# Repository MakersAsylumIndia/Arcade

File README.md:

# Arcade
A mini Arcade designed around two custom PCBs - the main board has the Arduino Nano, 128x64 I2C OLED display, and socket headers for digital, analog and PWM GPIO's. 

- The /enclosure folder has 3D FreeCAD model files.
- The /hardware_PCB folders contain schematic, PCB and related files.
- The /code folder has the Arduino code sketches.

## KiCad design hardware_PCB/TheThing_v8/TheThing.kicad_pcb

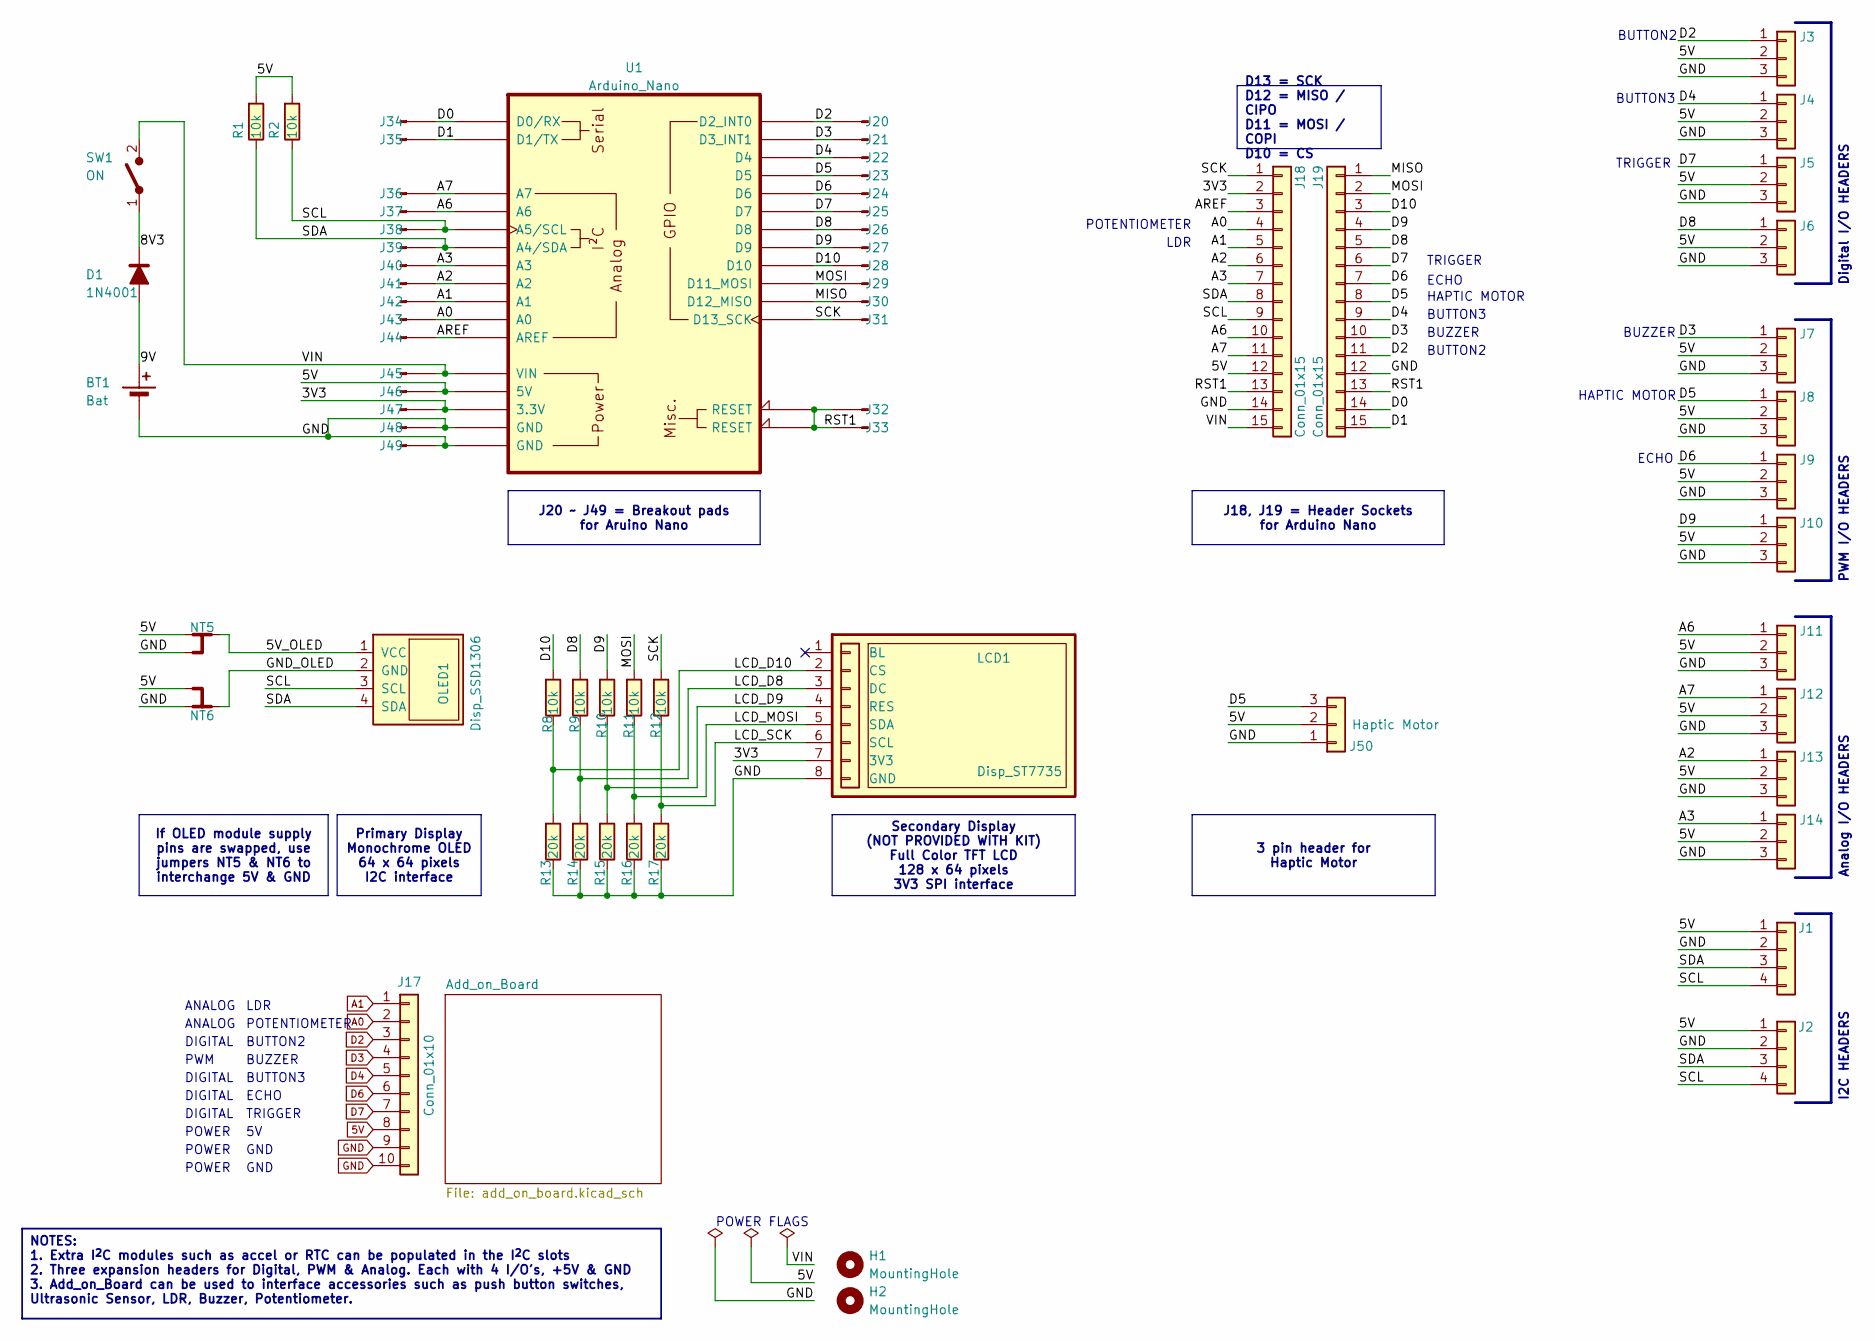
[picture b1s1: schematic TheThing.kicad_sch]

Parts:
BT1: Bat; PinHeader_1x02_P2.54mm_Horizontal
D1: 1N4001; D_DO-41_SOD81_P10.16mm_Horizontal
H1, H2: MountingHole; MountingHole_4.3mm_M4
J1, J2: Conn_I2C; PinHeader_1x04_P2.54mm_Vertical
J3, J4, J5, J6, J7, J8, J9, J10, J11, J12, J13, J14: Conn_01x03; PinHeader_1x03_P2.54mm_Vertical
J17: Conn_01x10; PinHeader_1x10_P2.54mm_Vertical
J18, J19: Conn_01x15; PinSocket_1x15_P2.54mm_Vertical
J20: D2; PinHeader_1x01_P2.54mm_Vertical
J21: D3; PinHeader_1x01_P2.54mm_Vertical
J22: D4; PinHeader_1x01_P2.54mm_Vertical
J23: D5; PinHeader_1x01_P2.54mm_Vertical
J24: D6; PinHeader_1x01_P2.54mm_Vertical
J25: D7; PinHeader_1x01_P2.54mm_Vertical
J26: D8; PinHeader_1x01_P2.54mm_Vertical
J27: D9; PinHeader_1x01_P2.54mm_Vertical
J28: D10; PinHeader_1x01_P2.54mm_Vertical
J29: D11; PinHeader_1x01_P2.54mm_Vertical
J30: D12; PinHeader_1x01_P2.54mm_Vertical
J31: D13; PinHeader_1x01_P2.54mm_Vertical
J32, J33: RST1; PinHeader_1x01_P2.54mm_Vertical
J34: D0; PinHeader_1x01_P2.54mm_Vertical
J35: D1; PinHeader_1x01_P2.54mm_Vertical
J36: A7; PinHeader_1x01_P2.54mm_Vertical
J37: A6; PinHeader_1x01_P2.54mm_Vertical
J38: A5; PinHeader_1x01_P2.54mm_Vertical
J39: A4; PinHeader_1x01_P2.54mm_Vertical
J40: A3; PinHeader_1x01_P2.54mm_Vertical
J41: A2; PinHeader_1x01_P2.54mm_Vertical
J42: A1; PinHeader_1x01_P2.54mm_Vertical
J43: A0; PinHeader_1x01_P2.54mm_Vertical
J44: AREF; PinHeader_1x01_P2.54mm_Vertical
J45: VIN; PinHeader_1x01_P2.54mm_Vertical
J46: 5V; PinHeader_1x01_P2.54mm_Vertical
J47: 3V3; PinHeader_1x01_P2.54mm_Vertical
J48: GND1; PinHeader_1x01_P2.54mm_Vertical
J49: GND2; PinHeader_1x01_P2.54mm_Vertical
J50: Conn_01x03; PinSocket_1x03_P2.54mm_Horizontal_haptic
LCD1: Disp_ST7735; Disp_TFT_LCD_128x128
NT5, NT6: NetTie_3; SolderJumper-3_P1.3mm_Bridged2Bar12_RoundedPad1.0x1.5mm_Num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
OLED1: Disp_SSD1306; Disp_128x64OLED
R1, R2, R8, R9, R10, R11, R12: 10k; R_Axial_DIN0207_L6.3mm_D2.5mm_P7.62mm_Horizontal
R13, R14, R15, R16, R17: 20k; R_Axial_DIN0207_L6.3mm_D2.5mm_P7.62mm_Horizontal
SW1: ON; SW_CuK_OS102011MA1QN1_SPDT_Angled
U1: Arduino_Nano; Arduino_Nano_v2_NoSPI

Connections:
5V: J1.1, J2.1, J3.2, J4.2, J5.2, J6.2, J7.2, J8.2, J9.2, J10.2, J11.2, J12.2, J13.2, J14.2, J17.8, J18.12, J46.1, J50.2, NT5.1, NT6.3, R1.1, R2.1, U1.5V
/3V3: J18.2, J47.1, LCD1.7 (3V3), U1.3V3 (3.3V)
/5V_OLED: NT5.2, OLED1.1 (VCC)
/8V3: D1.1 (K), SW1.1 (A)
/9V: BT1.1 (+), D1.2 (A)
/A2: J13.1, J18.6, J41.1, U1.A2
/A3: J14.1, J18.7, J40.1, U1.A3
/A6: J11.1, J18.10, J37.1, U1.A6
/A7: J12.1, J18.11, J36.1, U1.A7
/AREF: J18.3, J44.1, U1.AREF
/D0: J19.14, J34.1, U1.D0 (D0/RX)
/D1: J19.15, J35.1, U1.D1 (D1/TX)
/D5: J8.1, J19.8, J23.1, J50.3, U1.D5
/D8: J6.1, J19.5, J26.1, R9.1, U1.D8
/D9: J10.1, J19.4, J27.1, R10.1, U1.D9
/D10: J19.3, J28.1, R8.1, U1.D10
/GND_OLED: NT6.2, OLED1.2 (GND)
/LCD_D8: LCD1.3 (DC), R9.2, R14.1
/LCD_D9: LCD1.4 (RES), R10.2, R15.1
/LCD_D10: LCD1.2 (CS), R8.2, R13.1
/LCD_MOSI: LCD1.5 (SDA), R11.2, R16.1
/LCD_SCK: LCD1.6 (SCL), R12.2, R17.1
/MISO: J19.1, J30.1, U1.D12 (D12_MISO)
/MOSI: J19.2, J29.1, R11.1, U1.D11 (D11_MOSI)
/RST1: J18.13, J19.13, J32.1, J33.1, U1.RST1 (RESET), U1.RST2 (RESET)
/SCK: J18.1, J31.1, R12.1, U1.D13 (D13_SCK)
/SCL: J1.4, J2.4, J18.9, J38.1, OLED1.3 (SCL), R2.2, U1.A5 (A5/SCL)
/SDA: J1.3, J2.3, J18.8, J39.1, OLED1.4 (SDA), R1.2, U1.A4 (A4/SDA)
/VIN: J18.15, J45.1, SW1.2 (B), U1.VIN
A0: J17.2, J18.4, J43.1, U1.A0
A1: J17.1, J18.5, J42.1, U1.A1
D2: J3.1, J17.3, J19.11, J20.1, U1.D2 (D2_INT0)
D3: J7.1, J17.4, J19.10, J21.1, U1.D3 (D3_INT1)
D4: J4.1, J17.5, J19.9, J22.1, U1.D4
D6: J9.1, J17.6, J19.7, J24.1, U1.D6
D7: J5.1, J17.7, J19.6, J25.1, U1.D7
GND: BT1.2 (-), J1.2, J2.2, J3.3, J4.3, J5.3, J6.3, J7.3, J8.3, J9.3, J10.3, J11.3, J12.3, J13.3, J14.3, J17.9, J17.10, J18.14, J19.12, J48.1, J49.1, J50.1, LCD1.8 (GND), NT5.3, NT6.1, R13.2, R14.2, R15.2, R16.2, R17.2, U1.GND1 (GND), U1.GND2 (GND)

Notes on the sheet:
DIGITAL
BUTTON3
POWER
TRIGGER
BUZZER
Digital I/O HEADERS
I2C HEADERS
POTENTIOMETER
LDR
POWER FLAGS
PWM
ECHO
PWM I/O HEADERS
ANALOG
Analog I/O HEADERS
GND
HAPTIC MOTOR
BUTTON2
Primary Display Monochrome OLED 64 x 64 pixels I2C interface
D13 = SCK D12 = MISO / CIPO D11 = MOSI / COPI D10 = CS
J18, J19 = Header Sockets for Arduino Nano
3 pin header for Haptic Motor
Secondary Display (NOT PROVIDED WITH KIT) Full Color TFT LCD 128 x 64 pixels 3V3 SPI interface
NOTES: 1. Extra I^{2}C modules such as accel or RTC can be populated in the I^{2}C slots 2. Three expansion headers for Digital, PWM & Analog. Each with 4 I/O's, +5V & GND 3. Add_on_Board can be used to interface accessories such as push button switches, Ultrasonic Sensor, LDR, Buzzer, Potentiomete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
J20 ~ J49 = Breakout pads for Aruino Nano
If OLED module supply pins are swapped, use jumpers NT5 & NT6 to interchange 5V & GND

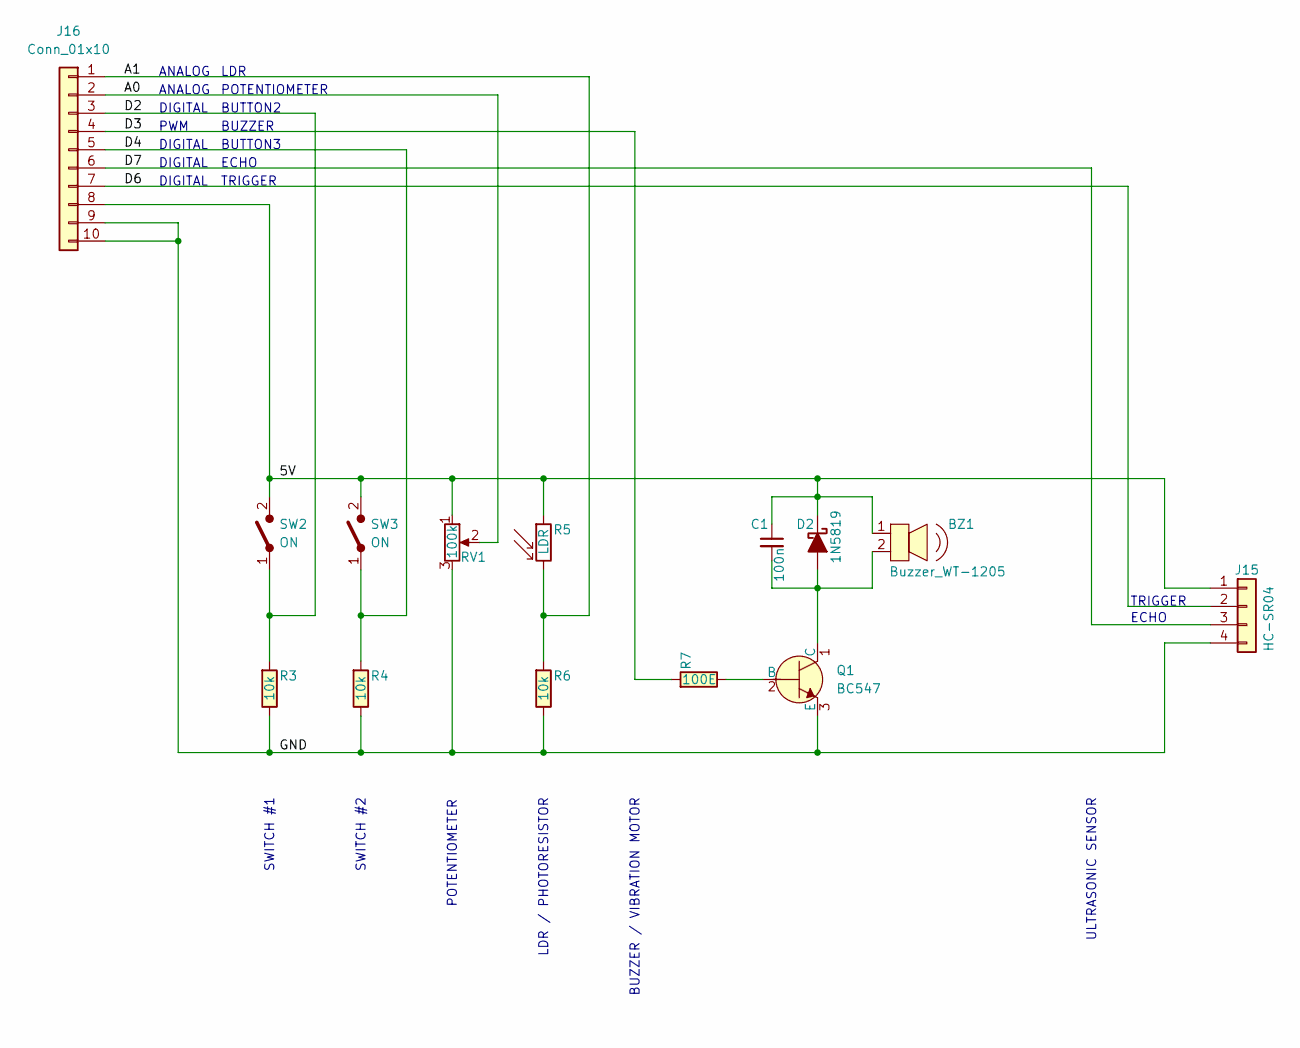
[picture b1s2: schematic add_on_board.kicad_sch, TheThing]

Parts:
BZ1: Buzzer_WT-1205; Buzzer_12x9.5RM7.6; MPN PS1240P02BT
C1: 100n; C_Disc_D3.0mm_W2.0mm_P2.50mm
D2: 1N5819; D_DO-41_SOD81_P10.16mm_Horizontal
J15: HC-SR04; PinSocket_1x04_P2.54mm_Vertical
J16: Conn_01x10; PinHeader_1x10_P2.54mm_Vertical
Q1: BC547; TO-92_HandSolder; MPN BC547B
R3, R4, R6: 10k; R_Axial_DIN0207_L6.3mm_D2.5mm_P7.62mm_Horizontal
R5: LDR; R_LDR_4.9x4.2mm_P2.54mm_Vertical
R7: 100E; R_Axial_DIN0207_L6.3mm_D2.5mm_P7.62mm_Horizontal
RV1: 100k; TRIM_601040
SW2, SW3: ON; SWITCH_PUSH_6mm_12mm

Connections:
/Add_on_Board/5V: BZ1.1, C1.1, D2.1 (K), J15.1, J16.8, R5.1, RV1.1, SW2.2 (B), SW3.2 (B)
/Add_on_Board/A0: J16.2, RV1.2
/Add_on_Board/A1: J16.1, R5.2, R6.1
/Add_on_Board/D2: J16.3, R3.1, SW2.1 (A)
/Add_on_Board/D3: J16.4, R7.1
/Add_on_Board/D4: J16.5, R4.1, SW3.1 (A)
/Add_on_Board/D6: J15.2, J16.7
/Add_on_Board/D7: J15.3, J16.6
/Add_on_Board/GND: J15.4, J16.9, J16.10, Q1.3 (E), R3.2, R4.2, R6.2, RV1.3
unnamed: BZ1.2, C1.2, D2.2 (A), Q1.1 (C)
unnamed: Q1.2 (B), R7.2

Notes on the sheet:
SWITCH #1
BUZZER / VIBRATION MOTOR
SWITCH #2
ULTRASONIC SENSOR
ANALOG
DIGITAL
PWM
BUZZER
BUTTON2
LDR / PHOTORESISTOR
POTENTIOMETER
ECHO
LDR
BUTTON3
TRIGGER

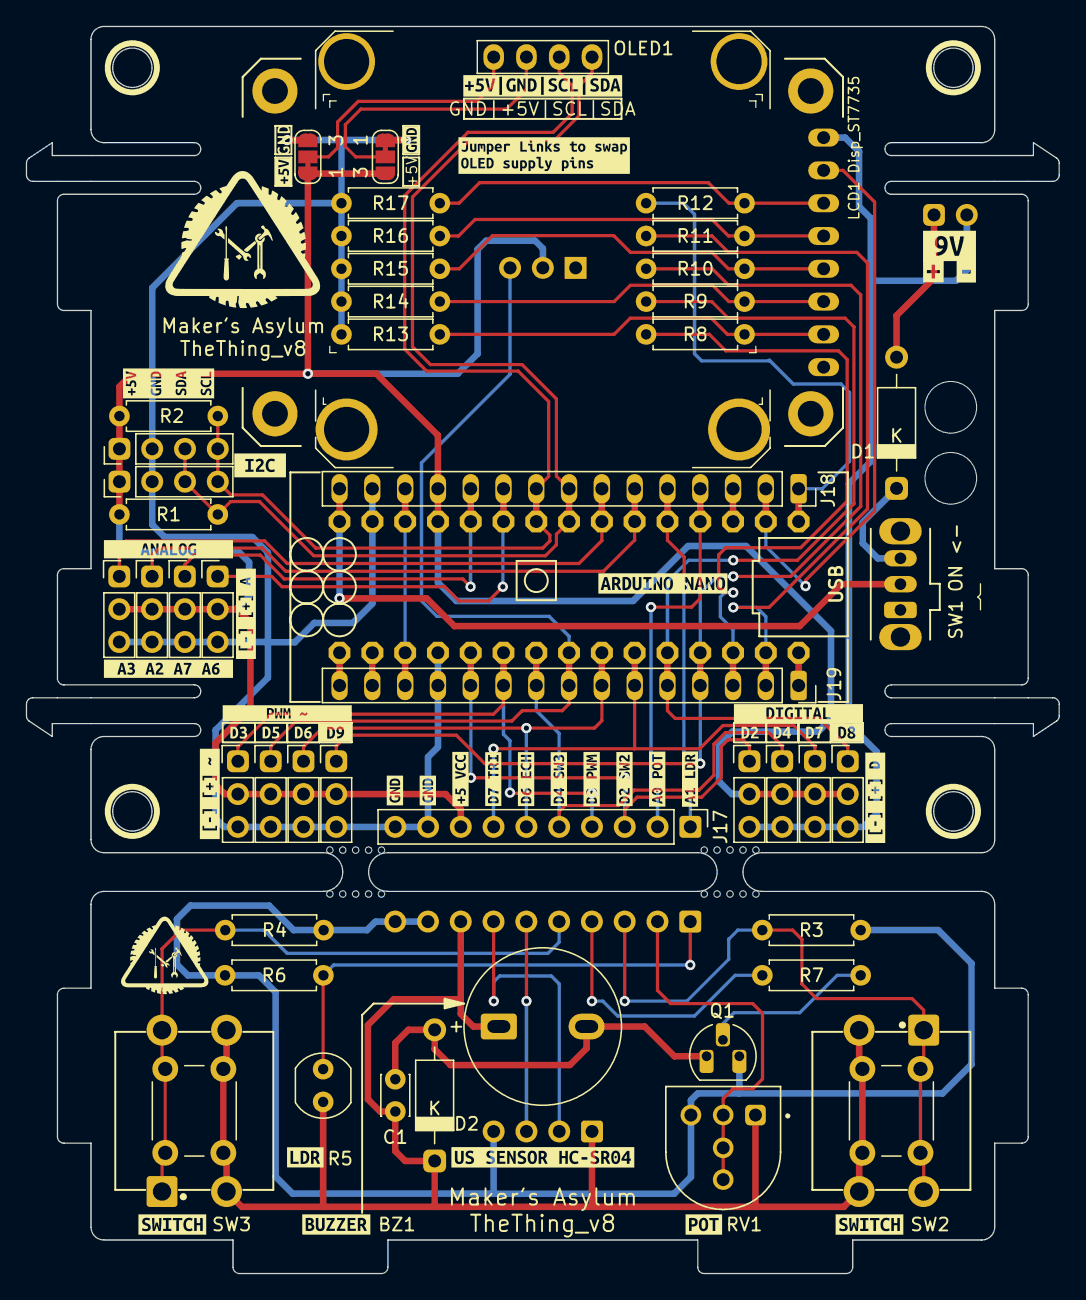
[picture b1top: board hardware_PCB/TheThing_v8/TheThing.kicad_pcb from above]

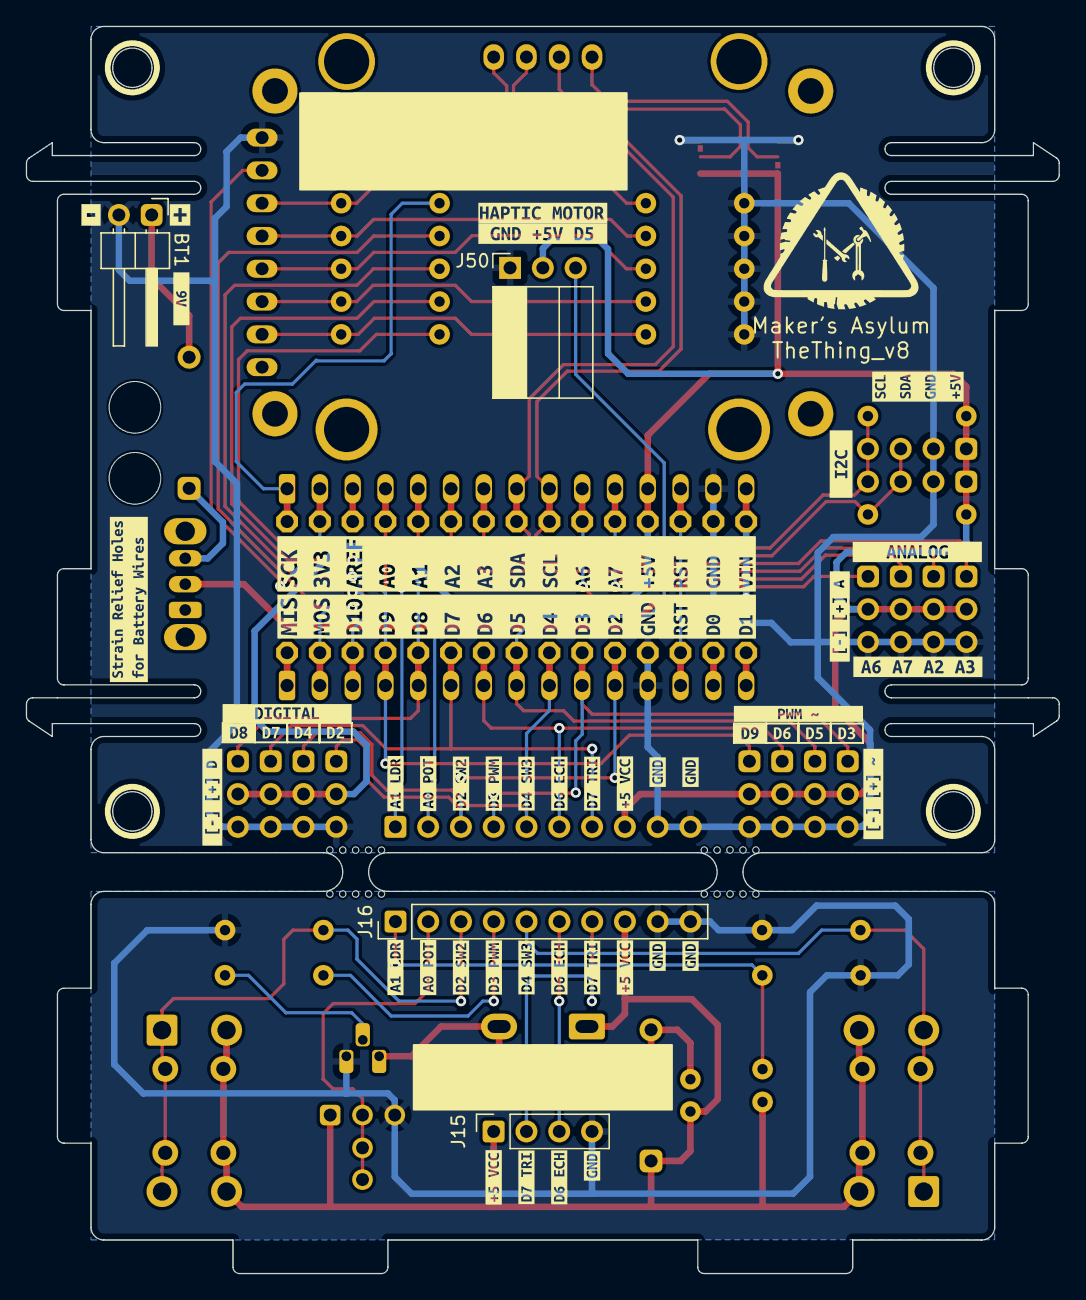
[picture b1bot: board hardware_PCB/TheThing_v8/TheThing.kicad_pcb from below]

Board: 2 copper layers, 80.0 x 96.6 mm, 173 parts (53 on the bottom side), 48 nets.

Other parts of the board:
kibuzzard-67A22DCA: G***; kibuzzard-67A22DCA
kibuzzard-67A22DD3: G***; kibuzzard-67A22DD3
kibuzzard-67A22DDD: G***; kibuzzard-67A22DDD
kibuzzard-67A22DE4: G***; kibuzzard-67A22DE4
kibuzzard-67A22DF7: G***; kibuzzard-67A22DF7
kibuzzard-67A122A3: G***; kibuzzard-67A122A3
kibuzzard-67A122C1: G***; kibuzzard-67A122C1
kibuzzard-67A11942: G***; kibuzzard-67A11942
kibuzzard-67A20273: G***; kibuzzard-67A20273
kibuzzard-681BBDCE: G***; kibuzzard-681BBDCE
kibuzzard-681CE6A6, kibuzzard-681CE6A6#2, kibuzzard-681CE6A6#3: G***; kibuzzard-681CE6A6
kibuzzard-681CE6D9, kibuzzard-681CE6D9#2, kibuzzard-681CE6D9#3: G***; kibuzzard-681CE6D9
kibuzzard-681CE6E0, kibuzzard-681CE6E0#2, kibuzzard-681CE6E0#3: G***; kibuzzard-681CE6E0
kibuzzard-681CE6FF, kibuzzard-681CE6FF#2, kibuzzard-681CE6FF#3: G***; kibuzzard-681CE6FF
kibuzzard-681CE70B, kibuzzard-681CE70B#2, kibuzzard-681CE70B#3: G***; kibuzzard-681CE70B
kibuzzard-681CE705, kibuzzard-681CE705#2, kibuzzard-681CE705#3: G***; kibuzzard-681CE705
kibuzzard-681CE710, kibuzzard-681CE710#2, kibuzzard-681CE710#3: G***; kibuzzard-681CE710
kibuzzard-681CE715, kibuzzard-681CE715#2, kibuzzard-681CE715#3: G***; kibuzzard-681CE715
kibuzzard-681CED7D: G***; kibuzzard-681CED7D
kibuzzard-681CEDBE: G***; kibuzzard-681CEDBE
kibuzzard-681CEE16: G***; kibuzzard-681CEE16
kibuzzard-681CEF1C: G***; kibuzzard-681CEF1C
kibuzzard-681CF111: G***; kibuzzard-681CF111
kibuzzard-681D00EA: G***; kibuzzard-681D00EA
kibuzzard-681D13E1, kibuzzard-681D13E1#2: G***; kibuzzard-681D13E1
kibuzzard-681D14E6, kibuzzard-681D14E6#2: G***; kibuzzard-681D14E6
kibuzzard-681D0124: G***; kibuzzard-681D0124
kibuzzard-681D1422: G***; kibuzzard-681D1422
kibuzzard-687E01B3: G***; kibuzzard-687E01B3
kibuzzard-687E01EA: G***; kibuzzard-687E01EA
kibuzzard-687E01F5: G***; kibuzzard-687E01F5
kibuzzard-687E12B6: G***; kibuzzard-687E12B6
kibuzzard-687E019A: G***; kibuzzard-687E019A
kibuzzard-687E020C: G***; kibuzzard-687E020C
kibuzzard-687E0202: G***; kibuzzard-687E0202
kibuzzard-687E1831: G***; kibuzzard-687E1831
kibuzzard-688B0B7B, kibuzzard-688B0B7B#2: G***; kibuzzard-688B0B7B
kibuzzard-688B0B80, kibuzzard-688B0B80#2: G***; kibuzzard-688B0B80
kibuzzard-688B0B86, kibuzzard-688B0B86#2: G***; kibuzzard-688B0B86
kibuzzard-688B0CB0, kibuzzard-688B0CB0#2: G***; kibuzzard-688B0CB0
kibuzzard-688B1C9E: G***; kibuzzard-688B1C9E
kibuzzard-688B4A2D: G***; kibuzzard-688B4A2D
kibuzzard-688B04F2: G***; kibuzzard-688B04F2
kibuzzard-688B05AD: G***; kibuzzard-688B05AD
kibuzzard-688B06AA, kibuzzard-688B06AA#2: G***; kibuzzard-688B06AA
kibuzzard-688B07C0, kibuzzard-688B07C0#2: G***; kibuzzard-688B07C0
kibuzzard-688B07DB, kibuzzard-688B07DB#2: G***; kibuzzard-688B07DB
kibuzzard-688B10BE: G***; kibuzzard-688B10BE
kibuzzard-688B11B5: G***; kibuzzard-688B11B5
kibuzzard-688B11BF: G***; kibuzzard-688B11BF
kibuzzard-688B21F2: G***; kibuzzard-688B21F2
kibuzzard-688B068F, kibuzzard-688B068F#2: G***; kibuzzard-688B068F
kibuzzard-6640C3B8: G***; kibuzzard-6640C3B8
kibuzzard-64612FA6, kibuzzard-64612FA6#2: G***; kibuzzard-64612FA6
kibuzzard-64612FED, kibuzzard-64612FED#2: G***; kibuzzard-64612FED
kibuzzard-68220AD1: G***; kibuzzard-68220AD1
kibuzzard-682711E3: G***; kibuzzard-682711E3
kibuzzard-682712AE: G***; kibuzzard-682712AE
kibuzzard-6461376B: G***; kibuzzard-6461376B
kibuzzard-6461377A: G***; kibuzzard-6461377A
kibuzzard-6827114F: G***; kibuzzard-6827114F
kibuzzard-68271661: G***; kibuzzard-68271661

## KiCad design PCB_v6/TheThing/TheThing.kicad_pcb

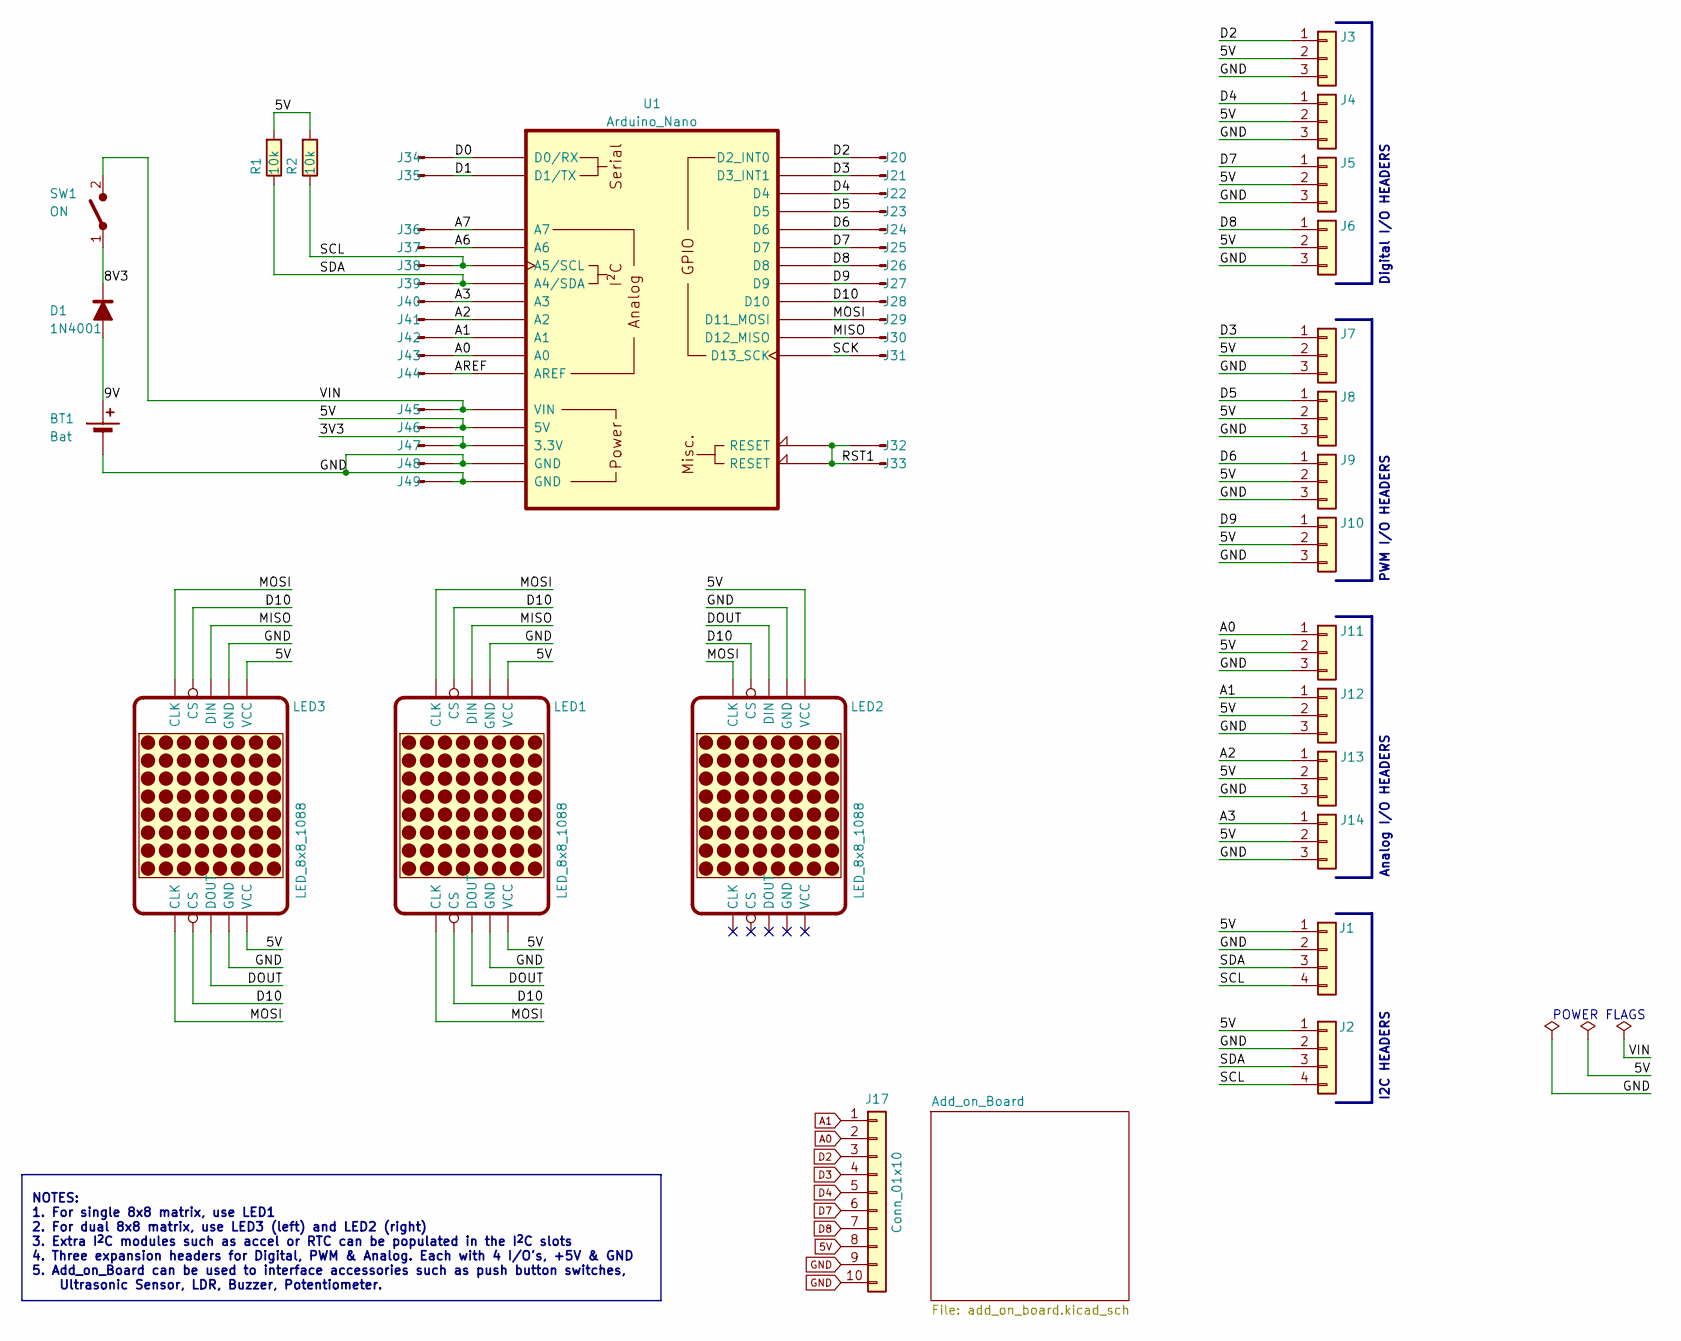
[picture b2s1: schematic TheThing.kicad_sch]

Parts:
BT1: Bat; PinHeader_1x02_P2.54mm_Vertical
D1: 1N4001; D_DO-41_SOD81_P10.16mm_Horizontal
J1, J2: Conn_I2C; PinHeader_1x04_P2.54mm_Vertical
J3, J4, J5, J6, J7, J8, J9, J10, J11, J12, J13, J14: Conn_01x03; PinHeader_1x03_P2.54mm_Vertical
J17: Conn_01x10; PinHeader_1x10_P2.54mm_Vertical
J20: D2; PinHeader_1x01_P2.54mm_Vertical
J21: D3; PinHeader_1x01_P2.54mm_Vertical
J22: D4; PinHeader_1x01_P2.54mm_Vertical
J23: D5; PinHeader_1x01_P2.54mm_Vertical
J24: D6; PinHeader_1x01_P2.54mm_Vertical
J25: D7; PinHeader_1x01_P2.54mm_Vertical
J26: D8; PinHeader_1x01_P2.54mm_Vertical
J27: D9; PinHeader_1x01_P2.54mm_Vertical
J28: D10; PinHeader_1x01_P2.54mm_Vertical
J29: D11; PinHeader_1x01_P2.54mm_Vertical
J30: D12; PinHeader_1x01_P2.54mm_Vertical
J31: D13; PinHeader_1x01_P2.54mm_Vertical
J32, J33: RST1; PinHeader_1x01_P2.54mm_Vertical
J34: D0; PinHeader_1x01_P2.54mm_Vertical
J35: D1; PinHeader_1x01_P2.54mm_Vertical
J36: A7; PinHeader_1x01_P2.54mm_Vertical
J37: A6; PinHeader_1x01_P2.54mm_Vertical
J38: A5; PinHeader_1x01_P2.54mm_Vertical
J39: A4; PinHeader_1x01_P2.54mm_Vertical
J40: A3; PinHeader_1x01_P2.54mm_Vertical
J41: A2; PinHeader_1x01_P2.54mm_Vertical
J42: A1; PinHeader_1x01_P2.54mm_Vertical
J43: A0; PinHeader_1x01_P2.54mm_Vertical
J44: AREF; PinHeader_1x01_P2.54mm_Vertical
J45: VIN; PinHeader_1x01_P2.54mm_Vertical
J46: 5V; PinHeader_1x01_P2.54mm_Vertical
J47: 3V3; PinHeader_1x01_P2.54mm_Vertical
J48: GND1; PinHeader_1x01_P2.54mm_Vertical
J49: GND2; PinHeader_1x01_P2.54mm_Vertical
LED1, LED2, LED3: LED_8x8_1088; LED_matrix_8x8_M1088
R1, R2: 10k; R_Axial_DIN0207_L6.3mm_D2.5mm_P7.62mm_Horizontal
SW1: ON; SW_CuK_OS102011MA1QN1_SPDT_Angled
U1: Arduino_Nano; Arduino_Nano_v2_NoSPI

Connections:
5V: J1.1, J2.1, J3.2, J4.2, J5.2, J6.2, J7.2, J8.2, J9.2, J10.2, J11.2, J12.2, J13.2, J14.2, J17.8, J46.1, LED1.VCC1 (VCC), LED1.VCC2 (VCC), LED2.VCC1 (VCC), LED3.VCC1 (VCC), LED3.VCC2 (VCC), R1.1, R2.1, U1.5V
/3V3: J47.1, U1.3V3 (3.3V)
/8V3: D1.1 (K), SW1.1 (A)
/9V: BT1.1 (+), D1.2 (A)
/A2: J13.1, J41.1, U1.A2
/A3: J14.1, J40.1, U1.A3
/A6: J37.1, U1.A6
/A7: J36.1, U1.A7
/AREF: J44.1, U1.AREF
/D0: J34.1, U1.D0 (D0/RX)
/D1: J35.1, U1.D1 (D1/TX)
/D5: J8.1, J23.1, U1.D5
/D6: J9.1, J24.1, U1.D6
/D9: J10.1, J27.1, U1.D9
/D10: J28.1, LED1.CS1 (CS), LED1.CS2 (CS), LED2.CS1 (CS), LED3.CS1 (CS), LED3.CS2 (CS), U1.D10
/DOUT: LED1.DOUT, LED2.DIN, LED3.DOUT
/MISO: J30.1, LED1.DIN, LED3.DIN, U1.D12 (D12_MISO)
/MOSI: J29.1, LED1.CLK1 (CLK), LED1.CLK2 (CLK), LED2.CLK1 (CLK), LED3.CLK1 (CLK), LED3.CLK2 (CLK), U1.D11 (D11_MOSI)
/RST1: J32.1, J33.1, U1.RST1 (RESET), U1.RST2 (RESET)
/SCK: J31.1, U1.D13 (D13_SCK)
/SCL: J1.4, J2.4, J38.1, R2.2, U1.A5 (A5/SCL)
/SDA: J1.3, J2.3, J39.1, R1.2, U1.A4 (A4/SDA)
/VIN: J45.1, SW1.2 (B), U1.VIN
A0: J11.1, J17.2, J43.1, U1.A0
A1: J12.1, J17.1, J42.1, U1.A1
D2: J3.1, J17.3, J20.1, U1.D2 (D2_INT0)
D3: J7.1, J17.4, J21.1, U1.D3 (D3_INT1)
D4: J4.1, J17.5, J22.1, U1.D4
D7: J5.1, J17.6, J25.1, U1.D7
D8: J6.1, J17.7, J26.1, U1.D8
GND: BT1.2 (-), J1.2, J2.2, J3.3, J4.3, J5.3, J6.3, J7.3, J8.3, J9.3, J10.3, J11.3, J12.3, J13.3, J14.3, J17.9, J17.10, J48.1, J49.1, LED1.GND1 (GND), LED1.GND2 (GND), LED2.GND1 (GND), LED3.GND1 (GND), LED3.GND2 (GND), U1.GND1 (GND), U1.GND2 (GND)

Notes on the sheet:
Digital I/O HEADERS
I2C HEADERS
POWER FLAGS
NOTES: 1. For single 8x8 matrix, use LED1 2. For dual 8x8 matrix, use LED3 (left) and LED2 (right) 3. Extra I^{2}C modules such as accel or RTC can be populated in the I^{2}C slots 4. Three expansion headers for Digital, PWM & Analog. Each with 4 I/O's, +5V & GND 5. Add_on_Board can be used to inte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
PWM I/O HEADERS
Analog I/O HEADERS

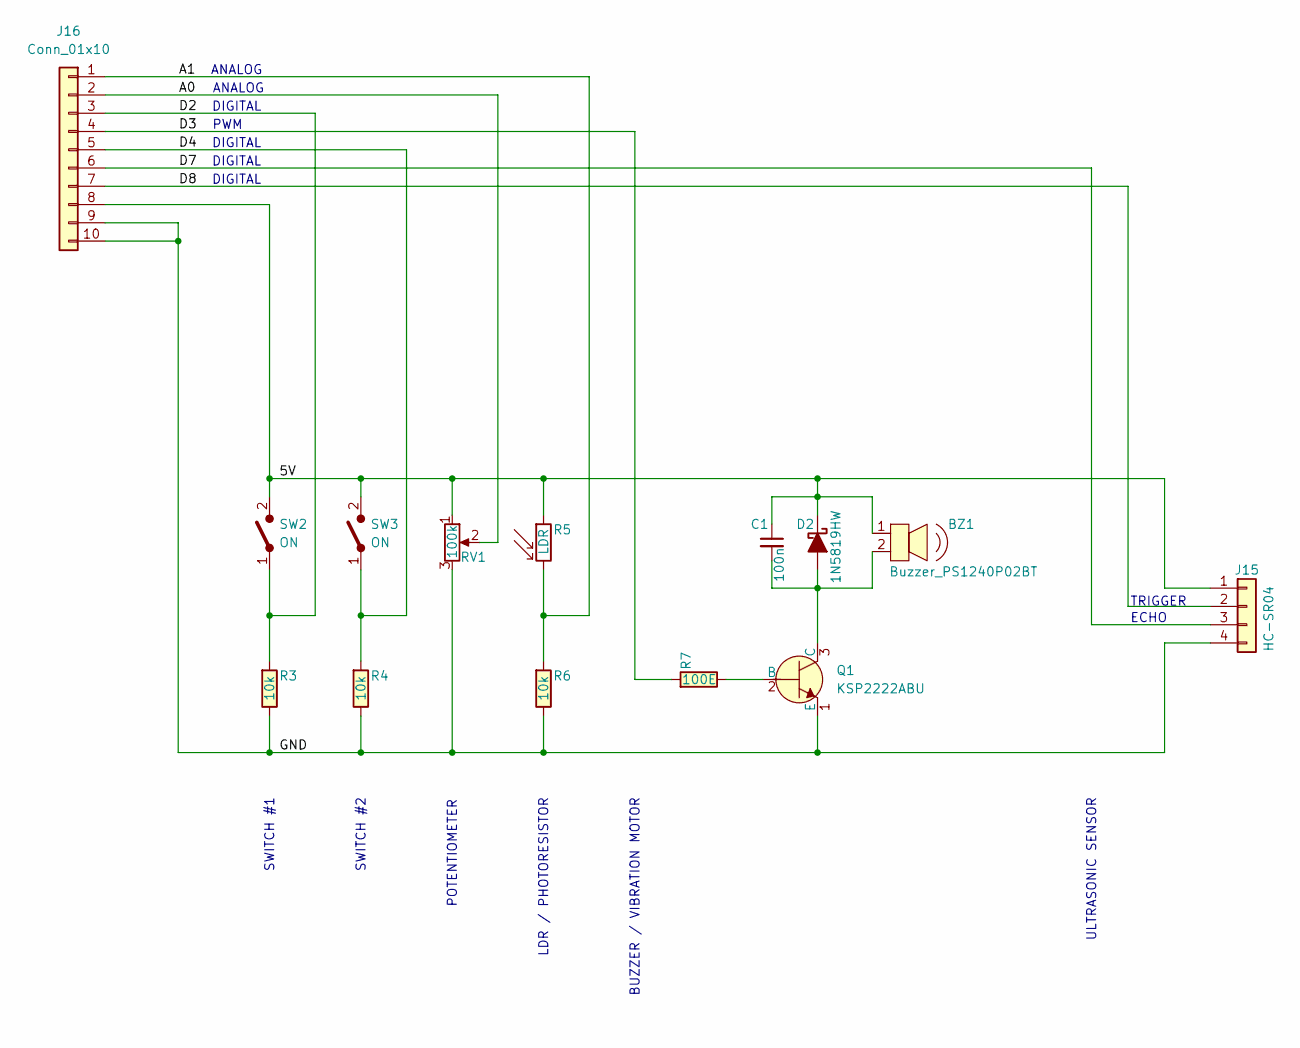
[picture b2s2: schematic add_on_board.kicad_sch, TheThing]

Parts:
BZ1: Buzzer_PS1240P02BT; Buzzer_12x9.5RM7.6; MPN PS1240P02BT; Digi-Key_PN 445-2525-1-ND
C1: 100n; C_Disc_D3.0mm_W2.0mm_P2.50mm
D2: 1N5819HW; D_DO-41_SOD81_P10.16mm_Horizontal
J15: HC-SR04; PinSocket_1x04_P2.54mm_Vertical
J16: Conn_01x10; PinHeader_1x10_P2.54mm_Vertical
Q1: KSP2222ABU; TO-92_HandSolder; MPN KSP2222ABU; Digi-Key_PN KSP2222ABUFS-ND
R3, R4, R6: 10k; R_Axial_DIN0207_L6.3mm_D2.5mm_P7.62mm_Horizontal
R5: LDR; R_LDR_4.9x4.2mm_P2.54mm_Vertical
R7: 100E; R_Axial_DIN0207_L6.3mm_D2.5mm_P7.62mm_Horizontal
RV1: 100k; TRIM_3352T-1-253LF
SW2, SW3: ON; SWITCH_PUSH_6mm_12mm

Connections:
/Add_on_Board/5V: BZ1.1, C1.1, D2.1 (K), J15.1, J16.8, R5.1, RV1.1, SW2.2 (B), SW3.2 (B)
/Add_on_Board/A0: J16.2, RV1.2
/Add_on_Board/A1: J16.1, R5.2, R6.1
/Add_on_Board/D2: J16.3, R3.1, SW2.1 (A)
/Add_on_Board/D3: J16.4, R7.1
/Add_on_Board/D4: J16.5, R4.1, SW3.1 (A)
/Add_on_Board/D7: J15.3, J16.6
/Add_on_Board/D8: J15.2, J16.7
/Add_on_Board/GND: J15.4, J16.9, J16.10, Q1.1 (E), R3.2, R4.2, R6.2, RV1.3
unnamed: BZ1.2, C1.2, D2.2 (A), Q1.3 (C)
unnamed: Q1.2 (B), R7.2

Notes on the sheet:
SWITCH #1
BUZZER / VIBRATION MOTOR
SWITCH #2
ULTRASONIC SENSOR
ANALOG
DIGITAL
PWM
LDR / PHOTORESISTOR
ECHO
TRIGGER
POTENTIOMETER

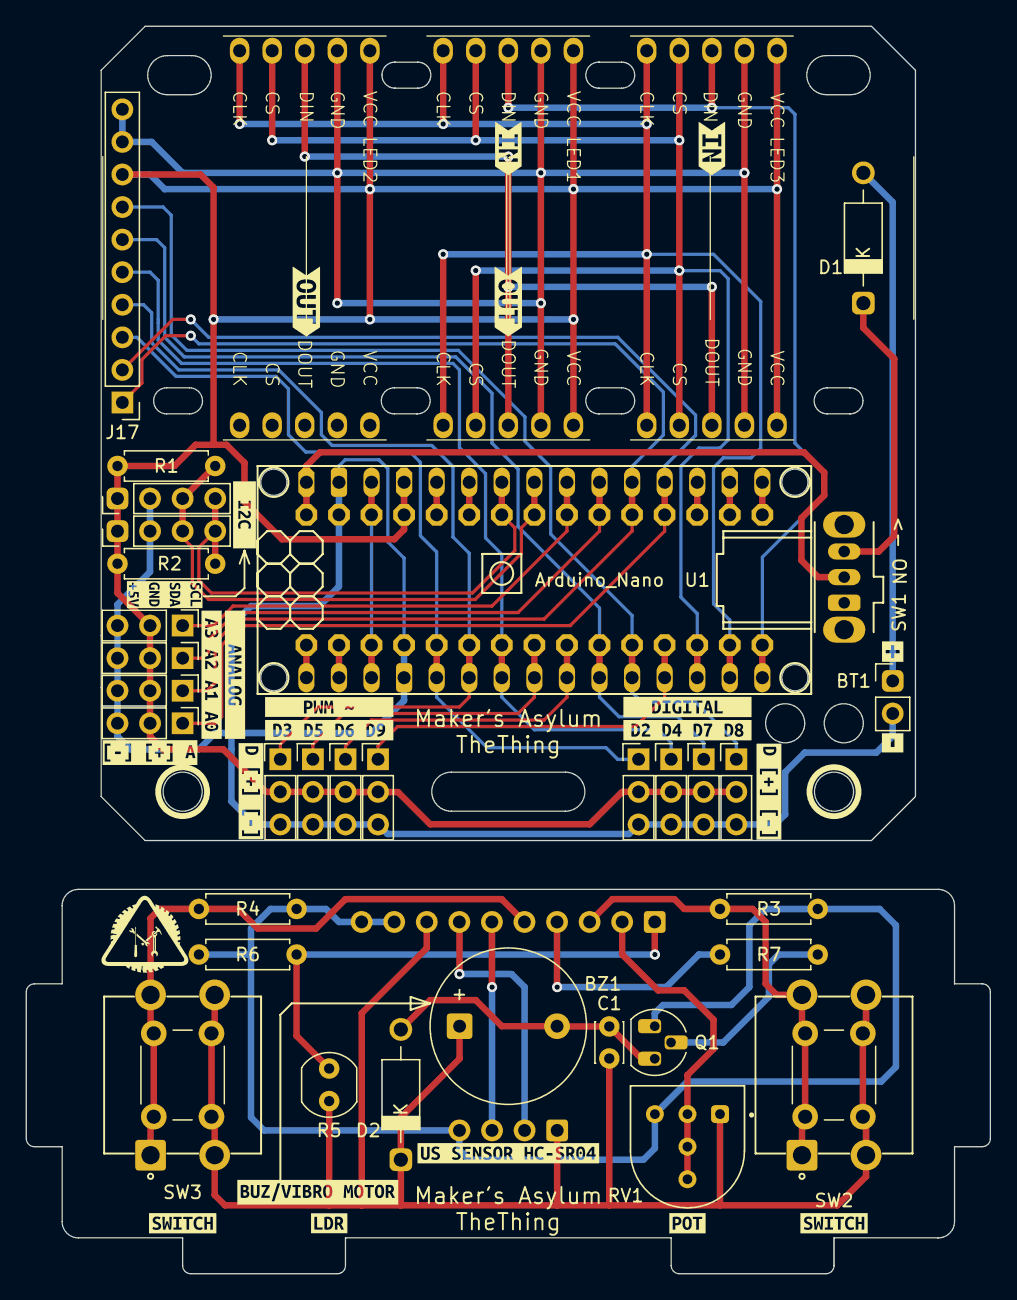
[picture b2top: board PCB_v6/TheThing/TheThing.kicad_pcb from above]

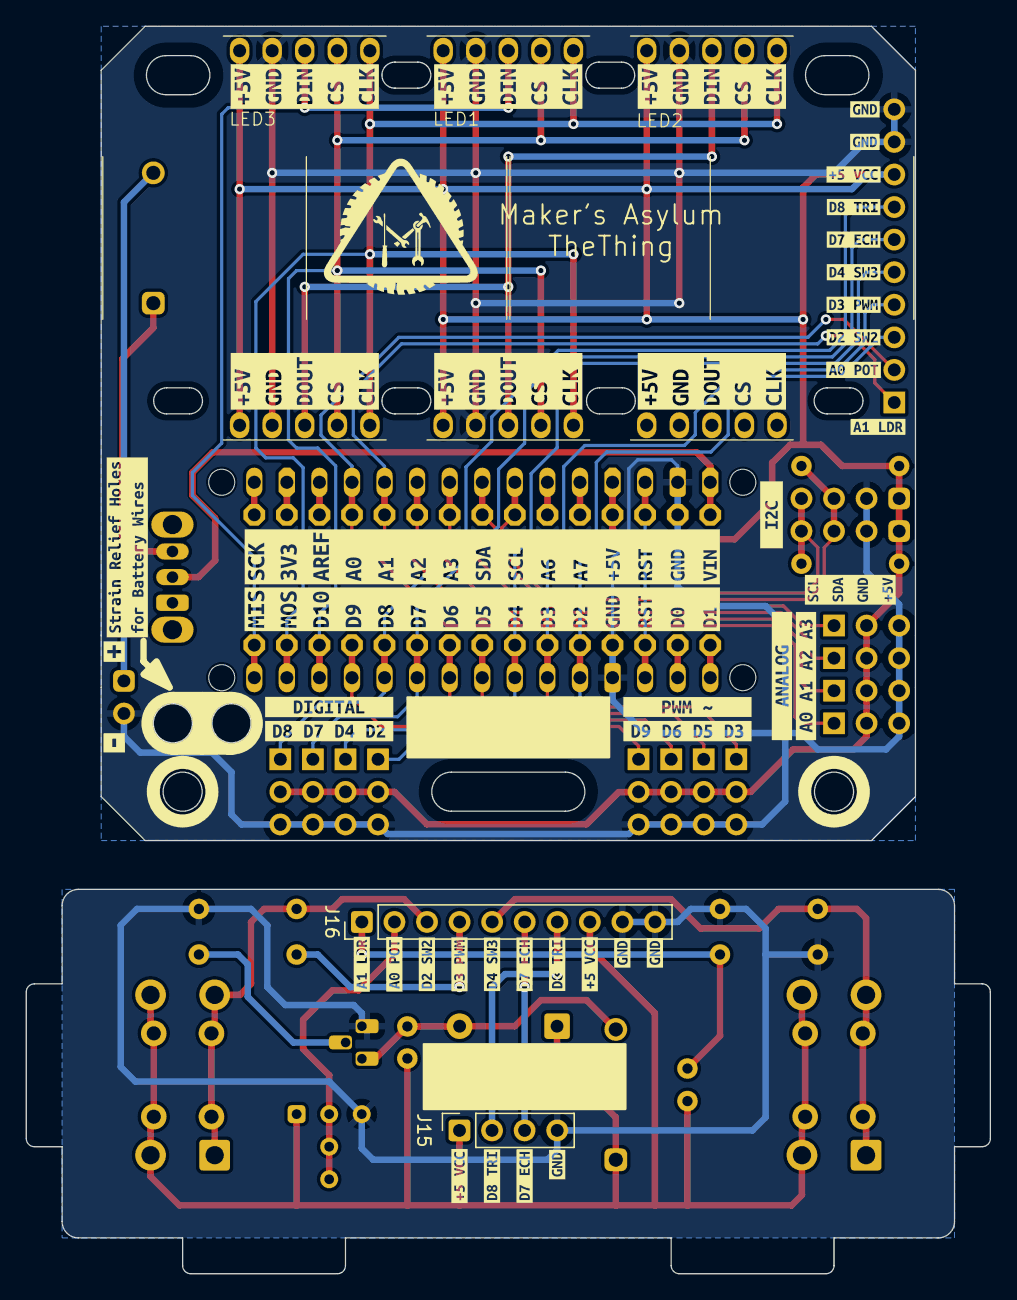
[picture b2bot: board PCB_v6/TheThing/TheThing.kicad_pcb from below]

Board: 2 copper layers, 75.2 x 97.3 mm, 134 parts (45 on the bottom side), 42 nets.

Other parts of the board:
kibuzzard-67A1FC5E: G***; kibuzzard-67A1FC5E
kibuzzard-67A1FC23: G***; kibuzzard-67A1FC23
kibuzzard-67A1FC29: G***; kibuzzard-67A1FC29
kibuzzard-67A1FC51: G***; kibuzzard-67A1FC51
kibuzzard-67A1FCC2: G***; kibuzzard-67A1FCC2
kibuzzard-67A1FCF1: G***; kibuzzard-67A1FCF1
kibuzzard-67A1FD26: G***; kibuzzard-67A1FD26
kibuzzard-67A11ADA, kibuzzard-67A11ADA#2: G***; kibuzzard-67A11ADA
kibuzzard-67A22DCA: G***; kibuzzard-67A22DCA
kibuzzard-67A22DD3: G***; kibuzzard-67A22DD3
kibuzzard-67A22DDD: G***; kibuzzard-67A22DDD
kibuzzard-67A22DE4: G***; kibuzzard-67A22DE4
kibuzzard-67A22DF7: G***; kibuzzard-67A22DF7
kibuzzard-67A22E24: G***; kibuzzard-67A22E24
kibuzzard-67A121CB, kibuzzard-67A121CB#2: G***; kibuzzard-67A121CB
kibuzzard-67A121DF, kibuzzard-67A121DF#2: G***; kibuzzard-67A121DF
kibuzzard-67A121F4, kibuzzard-67A121F4#2: G***; kibuzzard-67A121F4
kibuzzard-67A122A3, kibuzzard-67A122A3#2, kibuzzard-67A122A3#3: G***; kibuzzard-67A122A3
kibuzzard-67A122B8, kibuzzard-67A122B8#2: G***; kibuzzard-67A122B8
kibuzzard-67A122C1, kibuzzard-67A122C1#2, kibuzzard-67A122C1#3: G***; kibuzzard-67A122C1
kibuzzard-67A201C7: G***; kibuzzard-67A201C7
kibuzzard-67A201D4: G***; kibuzzard-67A201D4
kibuzzard-67A201FA: G***; kibuzzard-67A201FA
kibuzzard-67A1228F, kibuzzard-67A1228F#2: G***; kibuzzard-67A1228F
kibuzzard-67A2022B: G***; kibuzzard-67A2022B
kibuzzard-67A2040F: G***; kibuzzard-67A2040F
kibuzzard-67A2291F: G***; kibuzzard-67A2291F
kibuzzard-67A10623: G***; kibuzzard-67A10623
kibuzzard-67A11942: G***; kibuzzard-67A11942
kibuzzard-67A12228, kibuzzard-67A12228#2: G***; kibuzzard-67A12228
kibuzzard-67A12264, kibuzzard-67A12264#2: G***; kibuzzard-67A12264
kibuzzard-67A20214: G***; kibuzzard-67A20214
kibuzzard-67A20238: G***; kibuzzard-67A20238
kibuzzard-67A20268: G***; kibuzzard-67A20268
kibuzzard-67A20273: G***; kibuzzard-67A20273
kibuzzard-67A20403: G***; kibuzzard-67A20403
kibuzzard-67A20417: G***; kibuzzard-67A20417
kibuzzard-67A20431: G***; kibuzzard-67A20431
kibuzzard-67A20463: G***; kibuzzard-67A20463
kibuzzard-67A20470: G***; kibuzzard-67A20470
kibuzzard-67A22935: G***; kibuzzard-67A22935
kibuzzard-6461CA59, kibuzzard-6461CA59#2: G***; kibuzzard-6461CA59
kibuzzard-6461CA60, kibuzzard-6461CA60#2: G***; kibuzzard-6461CA60
kibuzzard-6640C3B8, kibuzzard-6640C3B8#2: G***; kibuzzard-6640C3B8
kibuzzard-64612FA6, kibuzzard-64612FA6#2: G***; kibuzzard-64612FA6
kibuzzard-64612FED, kibuzzard-64612FED#2: G***; kibuzzard-64612FED
kibuzzard-66412AF8: G***; kibuzzard-66412AF8
kibuzzard-6461376B: G***; kibuzzard-6461376B
kibuzzard-6461377A: G***; kibuzzard-6461377A
